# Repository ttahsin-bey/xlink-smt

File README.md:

# xlink-smt
Hardware compatible to xlink-project from Henning Bekel: http://henning-bekel.de/xlink/

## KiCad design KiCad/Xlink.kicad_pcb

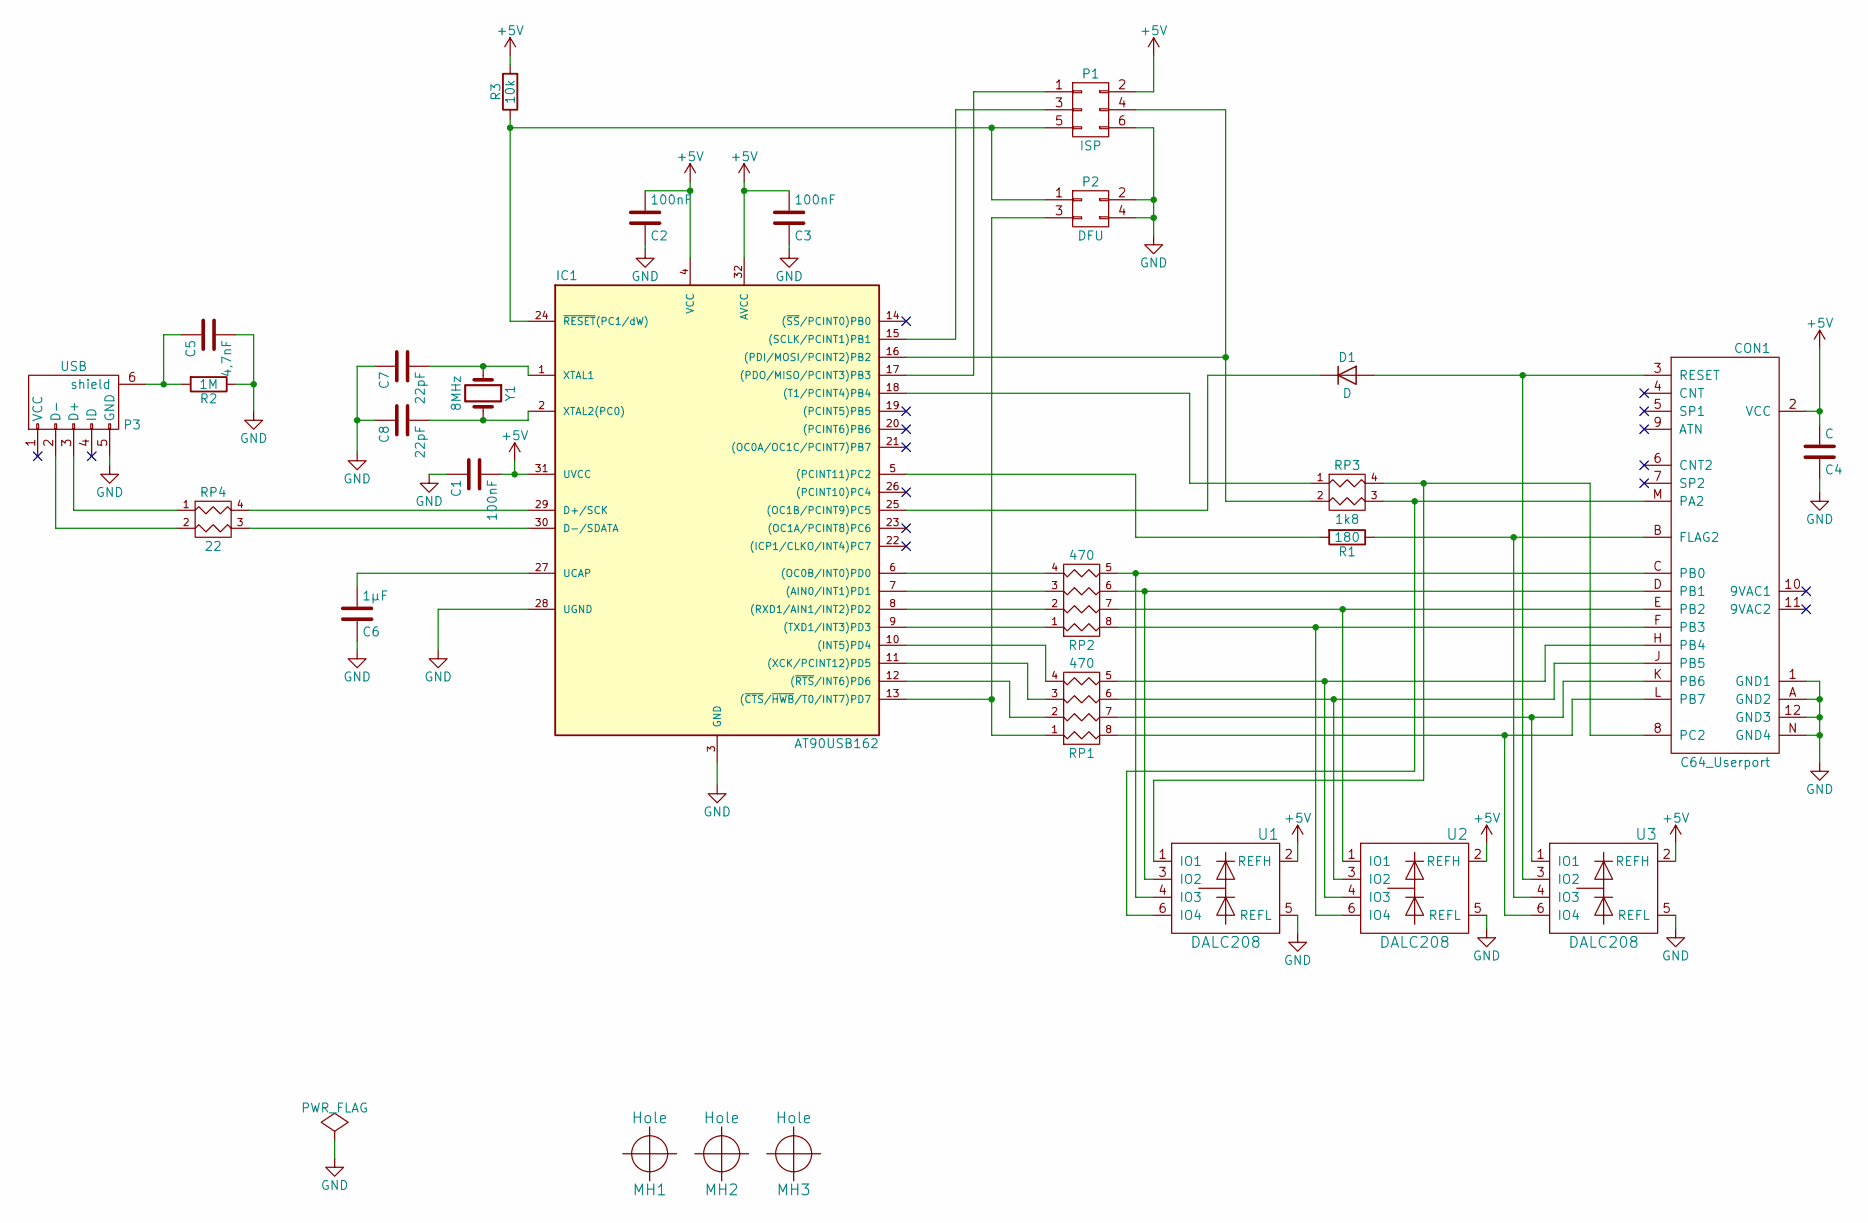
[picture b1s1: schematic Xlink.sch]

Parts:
C1, C2, C3: 100nF; TTB_C0603
C4: C; TTB_C0603
C5: 4,7nF; TTB_C0603
C6: 1µF; TTB_C0805
C7, C8: 22pF; TTB_C0603wide
CON1: C64_Userport; TTB_C64_Userport
D1: D; TTB_D0603
IC1: AT90USB162; TTB_TQFP32
MH1, MH2, MH3: Hole; MountingHole_3mm
P1: ISP; TTB_Pinhead_2x3
P2: DFU; TTB_Pinhead_2x2
P3: USB; TTB_USB-B_Micro_Würth
R1: 180; TTB_R0603
R2: 1M; TTB_R0603
R3: 10k; TTB_R0603
RP1, RP2: 470; TTB_RNet1206_4R
RP3: 1k8; TTB_RNet1206_2R
RP4: 22; TTB_RNet1206_2R
U1, U2, U3: DALC208; TTB_SOT23-6L
Y1: 8MHz; TTB_7A

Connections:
+5V: C1.2, C2.2, C3.2, C4.2, CON1.2 (VCC), IC1.4 (VCC), IC1.31 (UVCC), IC1.32 (AVCC), P1.2, R3.2, U1.2 (REFH), U2.2 (REFH), U3.2 (REFH)
GND: C1.1, C2.1, C3.1, C4.1, C5.2, C6.1, C7.1, C8.1, CON1.1 (GND1), CON1.12 (GND3), CON1.A (GND2), CON1.N (GND4), IC1.3 (GND), IC1.28 (UGND), P1.6, P2.2, P2.4, P3.5 (GND), R2.1, U1.5 (REFL), U2.5 (REFL), U3.5 (REFL)
unnamed: C5.1, P3.6 (shield), R2.2
unnamed: C6.2, IC1.27 (UCAP)
unnamed: C7.2, IC1.1 (XTAL1), Y1.1
unnamed: C8.2, IC1.2 (XTAL2(PC0)), Y1.2
unnamed: CON1.3 (RESET), D1.2 (A), U3.3 (IO2)
unnamed: CON1.8 (PC2), RP3.4 (R1), U1.1 (IO1)
unnamed: CON1.B (FLAG2), R1.1, U3.4 (IO3)
unnamed: CON1.C (PB0), RP2.5 (R4), U1.4 (IO3)
unnamed: CON1.D (PB1), RP2.6 (R3), U1.3 (IO2)
unnamed: CON1.E (PB2), RP2.7 (R2), U2.1 (IO1)
unnamed: CON1.F (PB3), RP2.8 (R1), U2.6 (IO4)
unnamed: CON1.H (PB4), RP1.5 (R4), U2.4 (IO3)
unnamed: CON1.J (PB5), RP1.6 (R3), U2.3 (IO2)
unnamed: CON1.K (PB6), RP1.7 (R2), U3.1 (IO1)
unnamed: CON1.L (PB7), RP1.8 (R1), U3.6 (IO4)
unnamed: CON1.M (PA2), RP3.3 (R2), U1.6 (IO4)
unnamed: D1.1 (K), IC1.25 ((OC1B/PCINT9)PC5)
unnamed: IC1.5 ((PCINT11)PC2), R1.2
unnamed: IC1.6 ((OC0B/INT0)PD0), RP2.4
unnamed: IC1.7 ((AIN0/INT1)PD1), RP2.3
unnamed: IC1.8 ((RXD1/AIN1/INT2)PD2), RP2.2
unnamed: IC1.9 ((TXD1/INT3)PD3), RP2.1
unnamed: IC1.10 ((INT5)PD4), RP1.4
unnamed: IC1.11 ((XCK/PCINT12)PD5), RP1.3
unnamed: IC1.12 ((~RTS~/INT6)PD6), RP1.2
unnamed: IC1.13 ((~CTS~/~HWB~/T0/INT7)PD7), P2.3, RP1.1
unnamed: IC1.15 ((SCLK/PCINT1)PB1), P1.3
unnamed: IC1.16 ((PDI/MOSI/PCINT2)PB2), P1.4, RP3.2
unnamed: IC1.17 ((PDO/MISO/PCINT3)PB3), P1.1
unnamed: IC1.18 ((T1/PCINT4)PB4), RP3.1
unnamed: IC1.24 (~RESET~(PC1/dW)), P1.5, P2.1, R3.1
unnamed: IC1.29 (D+/SCK), RP4.4 (R1)
unnamed: IC1.30 (D-/SDATA), RP4.3 (R2)
unnamed: P3.2 (D-), RP4.2
unnamed: P3.3 (D+), RP4.1

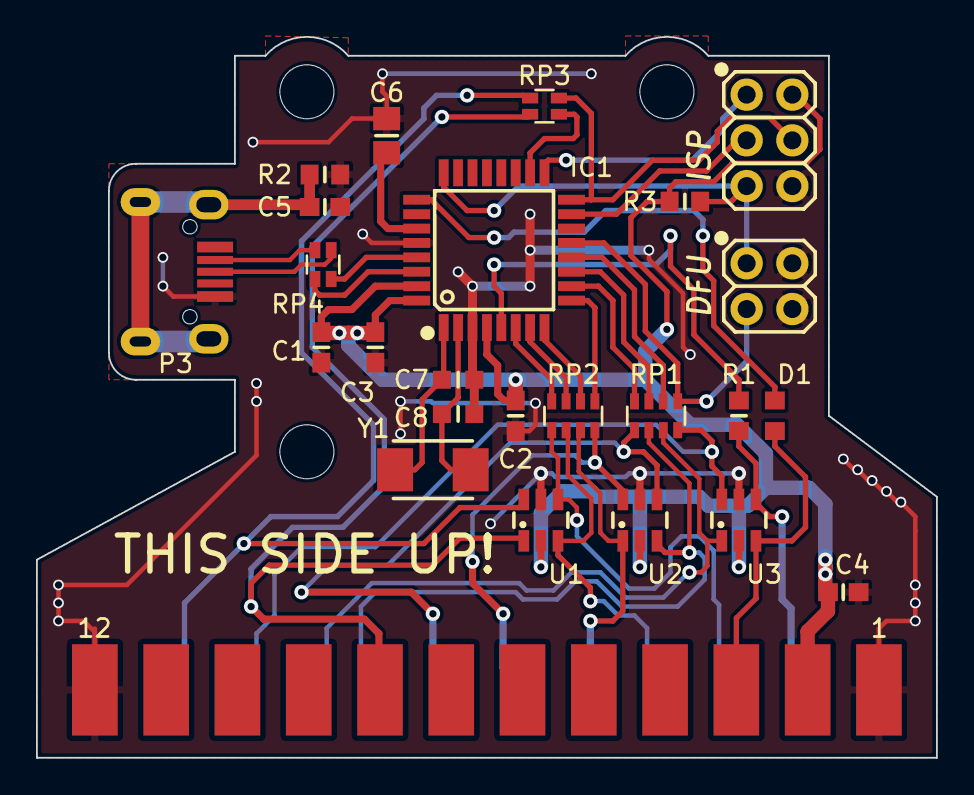
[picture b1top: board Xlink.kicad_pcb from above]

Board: 2 copper layers, 50.0 x 40.0 mm, 28 parts (0 on the bottom side), 37 nets.

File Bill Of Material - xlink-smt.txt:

Ref	Product		Package	Value			Distri	Order-Code

R1	Resistor	0603	180R, 1%		Mouser	603-RC0603FR-07180RL
R2	Resistor	0603	1M, 1%			Mouser	603-RC0603FR-071ML
R3	Resistor	0603	10k, 1%			Mouser	603-RC0603FR-0710KL

RP1	Resistor-4Net	0603	470R, 5%		Mouser	774-742C083471JP
RP2	Resistor-4Net	0603	470R, 5%		Mouser	774-742C083471JP
RP3	Resistor-2Net	0603	1k8, 5%			Mouser	774-742C043182JP
RP4	Resistor-2Net	0603	22R, 5%			Mouser	774-742C043220JP

C1	Capacitor	0603	100nF/50V, X7R, MLCC	Mouser	603-CC603KRX7R9BB104
C2	Capacitor	0603	100nF/50V, X7R, MLCC	Mouser	603-CC603KRX7R9BB104
C3	Capacitor	0603	100nF/50V, X7R, MLCC	Mouser	603-CC603KRX7R9BB104
C4	Capacitor	0603	100nF/50V, X7R, MLCC	Mouser	603-CC603KRX7R9BB104
C5	Capacitor	0603	4,7nF/50V, X7R, MLCC	Mouser	603-C0603KRX7R9BB472
C6	Capacitor	0603	1µF/25V, X7R, MLCC	Mouser	603-CC805KKX7R8BB105
C7	Capacitor	0603	22pF/25V, NP0, MLCC	Mouser	603-CC603JRNPO8BN220
C8	Capacitor	0603	22pF/25V, NP0, MLCC	Mouser	603-CC603JRNPO8BN220

D1	Diode		0603	1N4148			Reichlt	TS 4148-0603

Y1	Crystal		7A	8MHz, 18pF		Mouser	717-7A-8.000MAAJ-T

IC1	IC (CPU)	TQFP32	AT90USB162-16AU		Mouser	556-A90USB162-16AU

U1	IC		SOT23-6	DALC208SC6Y		Mouser	511-DALC208SC6
U2	IC		SOT23-6	DALC208SC6Y		Mouser	511-DALC208SC6
U3	IC		SOT23-6	DALC208SC6Y		Mouser	511-DALC208SC6

P1	ISP-Connector	n.a.	2*3 Pinheader 2,54mm	Reichlt	MPE 087-2-006		<-- DO NOT MOUNT!
P2	DFU-Connector	n.a.	2*2 Pinheader 2,54mm	Reichlt	MPE 087-2-004		<-- DO NOT MOUNT!
P3	USB-Connector	n.a.	Würth 629105150521	Mouser	710-629105150521

CON1	Userport-Con.

PCB	2 Layer, 1.2mm
